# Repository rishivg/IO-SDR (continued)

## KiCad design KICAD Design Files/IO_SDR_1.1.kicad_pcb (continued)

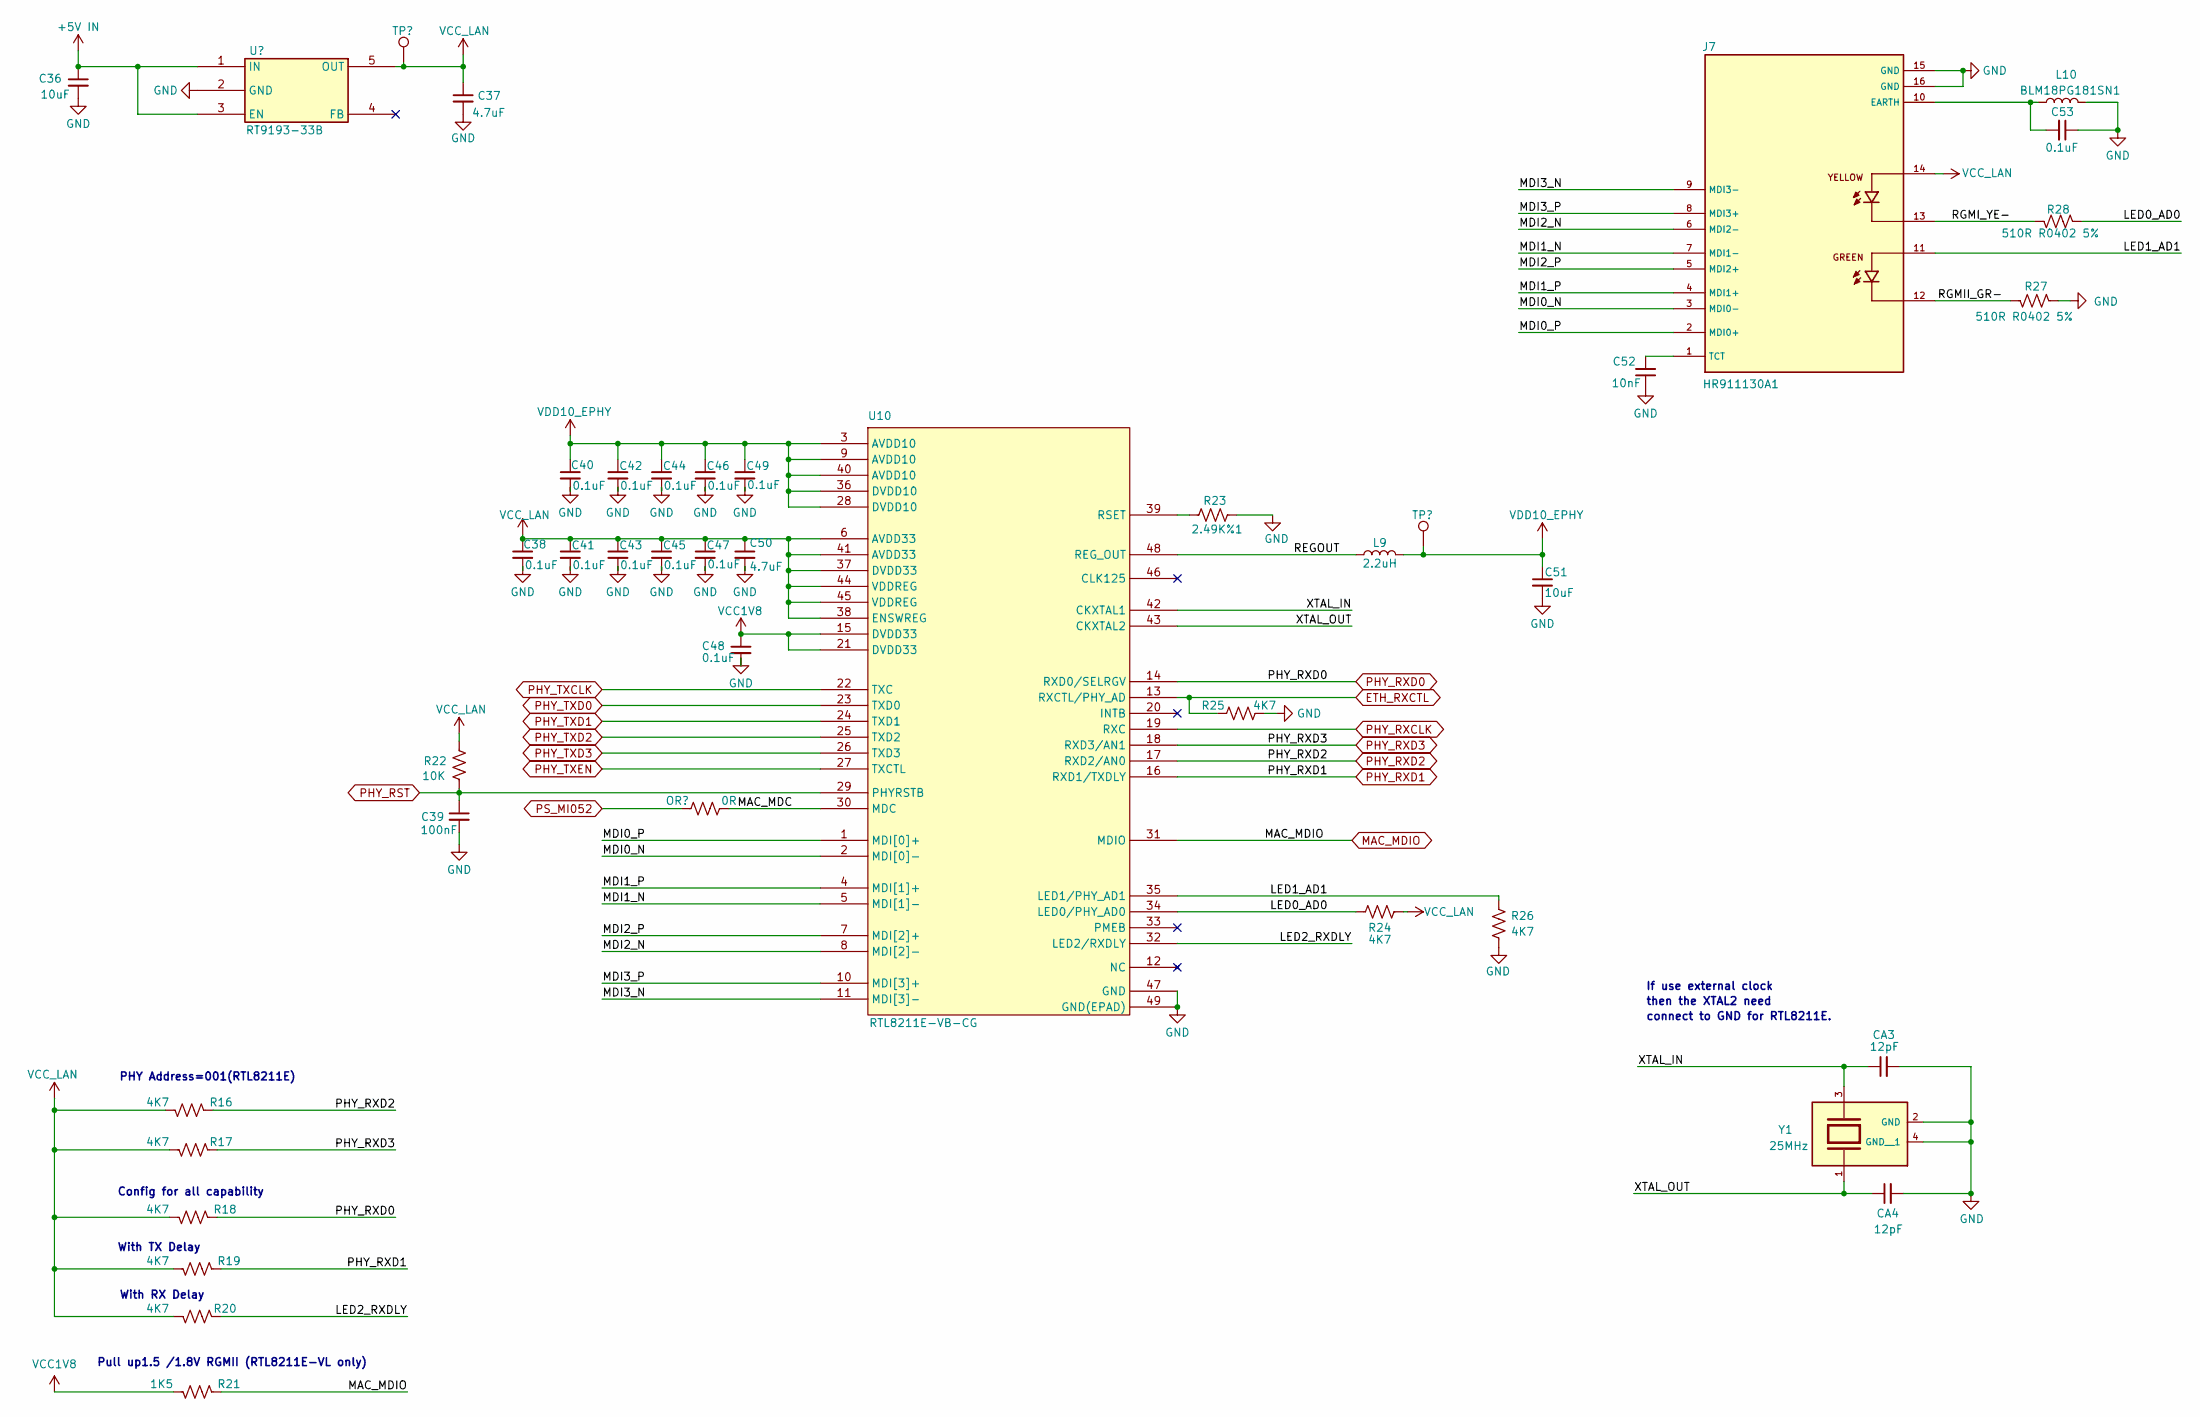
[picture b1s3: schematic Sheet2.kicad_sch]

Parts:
C36: 10uF; C_0603_1608Metric
C37, C50: 4.7uF; C_0603_1608Metric_Pad1.08x0.95mm_HandSolder
C38, C40, C41, C42, C43, C44, C45, C46, C47, C48, C49: 0.1uF; C_0402_1005Metric_Pad0.74x0.62mm_HandSolder
C39: 100nF; C_0402_1005Metric_Pad0.74x0.62mm_HandSolder
C51: 10uF; C_0805_2012Metric_Pad1.18x1.45mm_HandSolder
C52: 10nF; C_0402_1005Metric_Pad0.74x0.62mm_HandSolder
C53: 0.1uF; C_0805_2012Metric_Pad1.18x1.45mm_HandSolder
CA3, CA4: 12pF; C_0402_1005Metric_Pad0.74x0.62mm_HandSolder
J7: HR911130A1; HR911130A_HAN
L9: 2.2uH; L_0603_1608Metric_Pad1.05x0.95mm_HandSolder
L10: BLM18PG181SN1; L_0603_1608Metric_Pad1.05x0.95mm_HandSolder
R16, R17, R18, R19, R20, R24, R25, R26: 4K7; R_0402_1005Metric_Pad0.72x0.64mm_HandSolder
R21: 1K5; R_0402_1005Metric_Pad0.72x0.64mm_HandSolder
R22: 10K; R_0402_1005Metric_Pad0.72x0.64mm_HandSolder
R23: 2.49K%1; R_0402_1005Metric_Pad0.72x0.64mm_HandSolder
R27, R28: 510R R0402 5%; R_0402_1005Metric_Pad0.72x0.64mm_HandSolder
RA5: 0R; R_0603_1608Metric_Pad0.98x0.95mm_HandSolder
TP13, TP14: TestPoint; TestPoint_Pad_D1.0mm
U9: RT9193-33B
U10: RTL8211E-VB-CG
Y1: 25MHz; XTAL_TSX-3225_25.0000MF10P-C0; PARTREV N/A

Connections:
+1V8: C48.1, R21.1, U10.15 (DVDD33), U10.21 (DVDD33); also elsewhere on the board
+36V: C40.1, C42.1, C44.1, C46.1, C49.1, C51.1, L9.2, TP14.1, U10.3 (AVDD10), U10.9 (AVDD10), U10.28 (DVDD10), U10.36 (DVDD10), U10.40 (AVDD10)
/Sheet2/LED0_AD0: R24.2, R28.2, U10.34 (LED0/PHY_AD0)
/Sheet2/LED1_AD1: J7.11, R26.2, U10.35 (LED1/PHY_AD1)
/Sheet2/LED2_RXDLY: R20.2, U10.32 (LED2/RXDLY)
/Sheet2/MAC_MDC: RA5.1, U10.30 (MDC)
/Sheet2/MDI0_N: J7.3 (MDI0-), U10.2 (MDI[0]-)
/Sheet2/MDI0_P: J7.2 (MDI0+), U10.1 (MDI[0]+)
/Sheet2/MDI1_N: J7.7 (MDI1-), U10.5 (MDI[1]-)
/Sheet2/MDI1_P: J7.4 (MDI1+), U10.4 (MDI[1]+)
/Sheet2/MDI2_N: J7.6 (MDI2-), U10.8 (MDI[2]-)
/Sheet2/MDI2_P: J7.5 (MDI2+), U10.7 (MDI[2]+)
/Sheet2/MDI3_N: J7.9 (MDI3-), U10.11 (MDI[3]-)
/Sheet2/MDI3_P: J7.8 (MDI3+), U10.10 (MDI[3]+)
/Sheet2/REGOUT: L9.1, U10.48 (REG_OUT)
/Sheet2/RGMII_GR-: J7.12, R27.1
/Sheet2/RGMI_YE-: J7.13, R28.1
/Sheet2/XTAL_IN: CA3.1, U10.42 (CKXTAL1), Y1.3
/Sheet2/XTAL_OUT: CA4.1, U10.43 (CKXTAL2), Y1.1
ETH_RXCTL: R25.2, U10.13 (RXCTL/PHY_AD); also elsewhere on the board
GND: C36.2, C37.2, C38.2, C39.2, C40.2, C41.2, C42.2, C43.2, C44.2, C45.2, C46.2, C47.2, C48.2, C49.2, C50.2, C51.2, C52.1, C53.1, CA3.2, CA4.2, J7.15 (GND), J7.16 (GND), L10.1, R23.1, R25.1, R26.1, R27.2, U9.2 (GND), U10.47 (GND), U10.49 (GND(EPAD)), Y1.2 (GND), Y1.4 (GND__1); also elsewhere on the board
MAC_MDIO: R21.2, U10.31 (MDIO); also elsewhere on the board
unnamed: C53.2, J7.10 (EARTH), L10.2
unnamed: C52.2, J7.1 (TCT)
unnamed: R23.2, U10.39 (RSET)
PHY_RST: C39.1, R22.1, U10.29 (PHYRSTB)
PHY_RXCLK: U10.19 (RXC); also elsewhere on the board
PHY_RXD0: R18.2, U10.14 (RXD0/SELRGV); also elsewhere on the board
PHY_RXD1: R19.2, U10.16 (RXD1/TXDLY); also elsewhere on the board
PHY_RXD2: R16.2, U10.17 (RXD2/AN0); also elsewhere on the board
PHY_RXD3: R17.2, U10.18 (RXD3/AN1); also elsewhere on the board
PHY_TXCLK: U10.22 (TXC); also elsewhere on the board
PHY_TXD0: U10.23 (TXD0); also elsewhere on the board
PHY_TXD1: U10.24 (TXD1); also elsewhere on the board
PHY_TXD2: U10.25 (TXD2); also elsewhere on the board
PHY_TXD3: U10.26 (TXD3); also elsewhere on the board
PHY_TXEN: U10.27 (TXCTL); also elsewhere on the board
PS_MI052: RA5.2; also elsewhere on the board
VCC: C37.1, C38.1, C41.1, C43.1, C45.1, C47.1, C50.1, J7.14, R16.1, R17.1, R18.1, R19.1, R20.1, R22.2, R24.1, TP13.1, U9.5 (OUT), U10.6 (AVDD33), U10.37 (DVDD33), U10.38 (ENSWREG), U10.41 (AVDD33), U10.44 (VDDREG), U10.45 (VDDREG)

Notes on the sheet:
then the XTAL2 need
PHY Address=001(RTL8211E)
With RX Delay
Pull up1.5 /1.8V RGMII (RTL8211E-VL only)
connect to GND for RTL8211E.
If use external clock
Config for all capability
With TX Delay

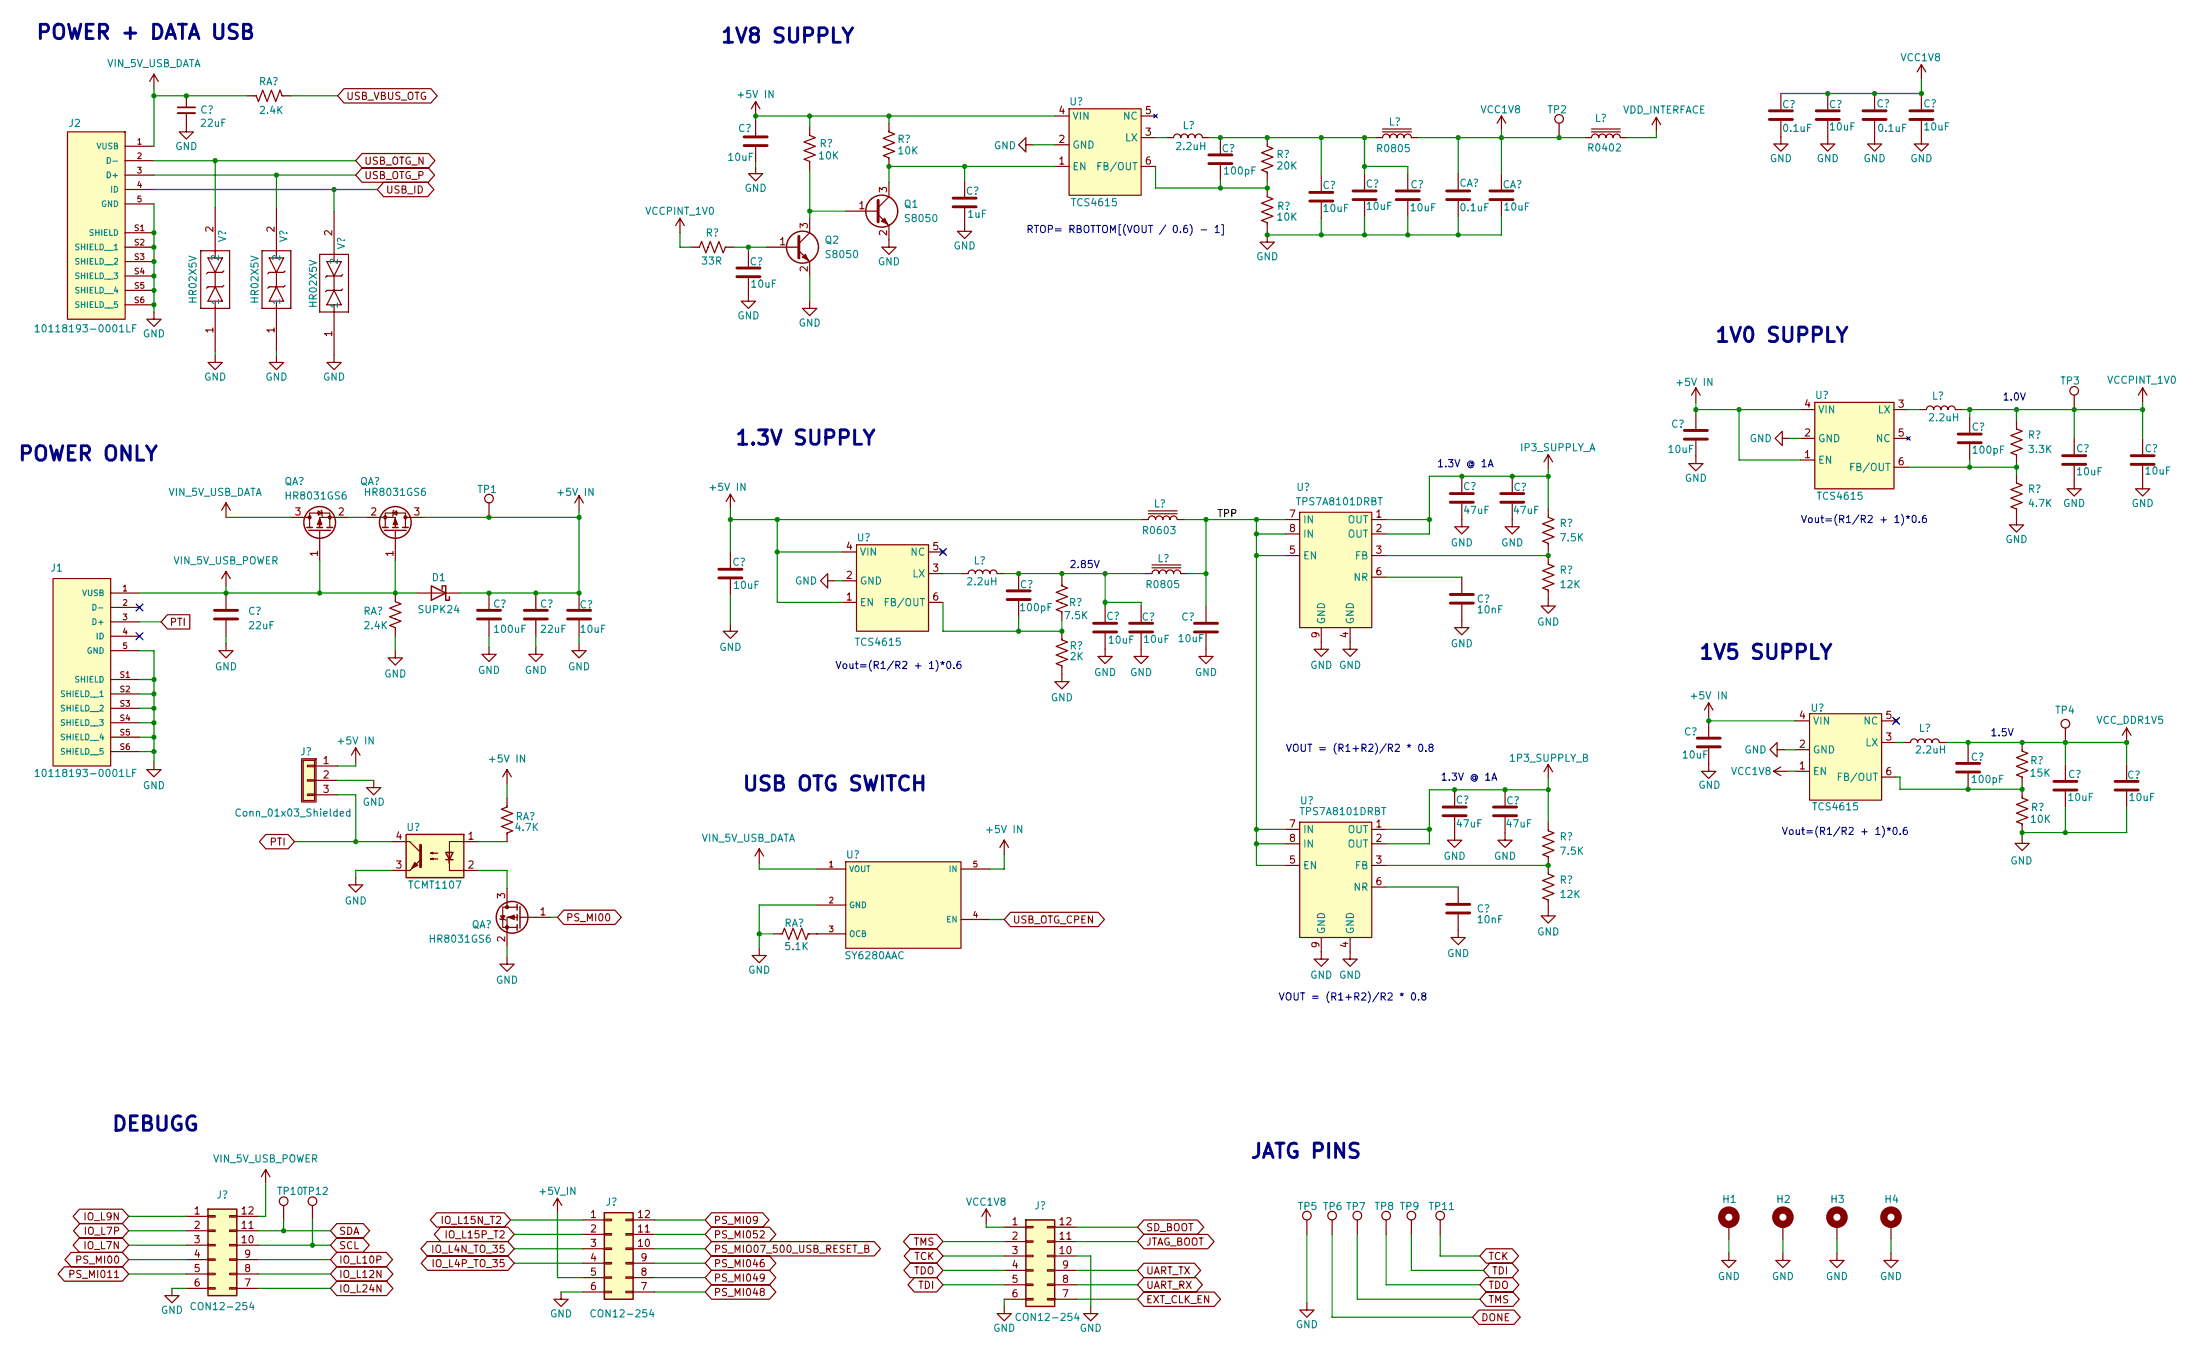
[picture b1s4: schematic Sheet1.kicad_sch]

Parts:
C1, C2: 22uF; C_1206_3216Metric_Pad1.33x1.80mm_HandSolder
C3: 100uF; C_0805_2012Metric_Pad1.18x1.45mm_HandSolder
C4: 22uF; C_0805_2012Metric_Pad1.18x1.45mm_HandSolder
C5: 10uF; C_0805_2012Metric_Pad1.18x1.45mm_HandSolder
C6, C11, C12, C13, C15, C16, C18, C19, C25, C28, C29, C32, C33, C34, C35: 10uF; C_0603_1608Metric_Pad1.08x0.95mm_HandSolder
C7, C8: 10uF; C_1206_3216Metric_Pad1.33x1.80mm_HandSolder
C9: 1uF; C_0805_2012Metric_Pad1.18x1.45mm_HandSolder
C10, C14, C30, C31: 100pF; C_0402_1005Metric_Pad0.74x0.62mm_HandSolder
C17, C20: 0.1uF; C_0402_1005Metric_Pad0.74x0.62mm_HandSolder
C21, C23, C26, C27: 47uF; C_1206_3216Metric_Pad1.33x1.80mm_HandSolder
C22, C24: 10nF; C_0402_1005Metric_Pad0.74x0.62mm_HandSolder
CA1: 0.1uF; C_0402_1005Metric_Pad0.74x0.62mm_HandSolder
CA2: 10uF; C_0603_1608Metric_Pad1.08x0.95mm_HandSolder
D1: SUPK24; D_SOD-123
H1, H2, H3, H4: MountingHole_Pad; MountingHole_2.5mm_Pad
J1, J2: 10118193-0001LF; AMPHENOL_10118193-0001LF; PARTREV E
J3: Conn_01x03_Shielded; PinHeader_1x03_P2.54mm_Vertical
J4, J5, J6: CON12-254; PinHeader_2x06_P2.54mm_Vertical
L1, L4, L7, L8: 2.2uH; L_0603_1608Metric_Pad1.05x0.95mm_HandSolder
L2: R0603; L_0603_1608Metric_Pad1.05x0.95mm_HandSolder
L3, L5: R0805; L_0805_2012Metric_Pad1.05x1.20mm_HandSolder
L6: R0402; L_0402_1005Metric_Pad0.77x0.64mm_HandSolder
Q1, Q2: S8050; SOT-23
QA1, QA2, QA3: HR8031GS6
R1: 33R; R_0402_1005Metric_Pad0.72x0.64mm_HandSolder
R2, R3, R7, R15: 10K; R_0402_1005Metric_Pad0.72x0.64mm_HandSolder
R4, R8, R10: 7.5K; R_0402_1005Metric_Pad0.72x0.64mm_HandSolder
R5: 2K; R_0402_1005Metric_Pad0.72x0.64mm_HandSolder
R6: 20K; R_0402_1005Metric_Pad0.72x0.64mm_HandSolder
R9, R11: 12K; R_0402_1005Metric_Pad0.72x0.64mm_HandSolder
R12: 3.3K; R_0402_1005Metric_Pad0.72x0.64mm_HandSolder
R13: 4.7K; R_0402_1005Metric_Pad0.72x0.64mm_HandSolder
R14: 15K; R_0402_1005Metric_Pad0.72x0.64mm_HandSolder
RA1, RA2: 2.4K; R_0402_1005Metric_Pad0.72x0.64mm_HandSolder
RA3: 4.7K; R_0603_1608Metric_Pad0.98x0.95mm_HandSolder
RA4: 5.1K; R_0603_1608Metric_Pad0.98x0.95mm_HandSolder
TP1, TP2, TP3, TP4, TP5, TP6, TP7, TP8, TP9, TP10, TP11, TP12: TestPoint; TestPoint_Pad_D1.0mm
U1: TCMT1107; SOP-4_4.4x2.6mm_P1.27mm
U2: SY6280AAC
U3, U4, U7, U8: TCS4615
U5, U6: TPS7A8101DRBT
V1, V2, V3: HR02X5V

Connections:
+1V0: C30.1, C32.1, C35.1, L8.2, R1.1, R12.1, TP3.1; also elsewhere on the board
+1V2: C21.1, C26.1, R10.1, U6.1 (OUT), U6.2 (OUT); also elsewhere on the board
+1V5: C31.1, C33.1, C34.1, L7.2, R14.1, TP4.1; also elsewhere on the board
+1V8: C17.1, C19.1, C20.1, C25.1, CA1.1, CA2.1, J5.1, L5.2, L6.1, TP2.1, U7.1 (EN); also elsewhere on the board
+5VD: C2.1, D1.2 (A), J1.1 (VUSB), J4.12, QA1.1 (G), QA2.1 (G), RA2.1
+5VP: C1.1, J2.1 (VUSB), QA1.3 (D), RA1.2, U2.1 (VOUT)
+12L: C23.1, C27.1, R8.1, U5.1 (OUT), U5.2 (OUT); also elsewhere on the board
+VSW: L6.2; also elsewhere on the board
/Sheet1/TPP: C13.1, L2.2, L3.2, U5.5 (EN), U5.7 (IN), U5.8 (IN), U6.5 (EN), U6.7 (IN), U6.8 (IN)
DONE: TP6.1; also elsewhere on the board
EXT_CLK_EN: J5.7; also elsewhere on the board
GND: C1.2, C2.2, C3.2, C4.2, C5.2, C6.2, C7.2, C8.2, C9.2, C11.2, C12.2, C13.2, C15.2, C16.2, C17.2, C18.2, C19.2, C20.2, C21.2, C22.2, C23.2, C24.2, C25.2, C26.2, C27.2, C28.2, C29.2, C32.2, C33.2, C34.2, C35.2, CA1.2, CA2.2, H1.1, H2.1, H3.1, H4.1, J1.5 (GND), J1.S1 (SHIELD), J1.S2 (SHIELD__1), J1.S3 (SHIELD__2), J1.S4 (SHIELD__3), J1.S5 (SHIELD__4), J1.S6 (SHIELD__5), J2.5 (GND), J2.S1 (SHIELD), J2.S2 (SHIELD__1), J2.S3 (SHIELD__2), J2.S4 (SHIELD__3), J2.S5 (SHIELD__4), J2.S6 (SHIELD__5), J3.2, J4.6, J5.6, J5.10, J6.6, Q1.2 (E), Q2.2 (E), QA3.2 (S), R5.2, R7.2, R9.2, R11.2, R13.2, R15.2, RA2.2, RA4.2, TP5.1, U1.3, U2.2 (GND), U3.2 (GND), U4.2 (GND), U5.4 (GND), U5.9 (GND), U6.4 (GND), U6.9 (GND), U7.2 (GND), U8.2 (GND), V1.1, V2.1, V3.1; also elsewhere on the board
IO_L4N_TO_35: J6.3; also elsewhere on the board
IO_L4P_TO_35: J6.4; also elsewhere on the board
IO_L7N: J4.3; also elsewhere on the board
IO_L7P: J4.2; also elsewhere on the board
IO_L9N: J4.1; also elsewhere on the board
IO_L10P: J4.9; also elsewhere on the board
IO_L12N: J4.8; also elsewhere on the board
IO_L15N_T2: J6.1
IO_L15P_T2: J6.2; also elsewhere on the board
IO_L24N: J4.7; also elsewhere on the board
JTAG_BOOT: J5.11; also elsewhere on the board
unnamed: C10.1, C11.1, C12.1, L1.2, L3.1, R4.1
unnamed: C14.1, C15.1, C16.1, C18.1, L4.2, L5.1, R6.1
unnamed: Q1.1 (B), Q2.3 (C), R2.2
unnamed: C9.1, Q1.3 (C), R3.2, U4.1 (EN)
unnamed: C7.1, Q2.1 (B), R1.2
unnamed: QA1.2 (S), QA2.2 (S)
unnamed: QA3.3 (D), U1.2
unnamed: RA3.2, U1.1
unnamed: RA4.1, U2.3 (OCB)
unnamed: C10.2, R4.2, R5.1, U3.6 (FB/OUT)
unnamed: L1.1, U3.3 (LX)
unnamed: C14.2, R6.2, R7.1, U4.6 (FB/OUT)
unnamed: L4.1, U4.3 (LX)
unnamed: R8.2, R9.1, U5.3 (FB)
unnamed: C24.1, U5.6 (NR)
unnamed: R10.2, R11.1, U6.3 (FB)
unnamed: C22.1, U6.6 (NR)
unnamed: C31.2, R14.2, R15.1, U7.6 (FB/OUT)
unnamed: L7.1, U7.3 (LX)
unnamed: C30.2, R12.2, R13.1, U8.6 (FB/OUT)
unnamed: L8.1, U8.3 (LX)
PS_MI00: J4.4, QA3.1 (G); also elsewhere on the board
PS_MI09: J6.12; also elsewhere on the board
PS_MI011: J4.5; also elsewhere on the board
PS_MI046: J6.9; also elsewhere on the board
PS_MI048: J6.7; also elsewhere on the board
PS_MI049: J6.8; also elsewhere on the board
PS_MI052: J6.11; also elsewhere on the board
PS_MIO07_500_USB_RESET_B: J6.10; also elsewhere on the board
PTI: J1.3 (D+), J3.3, U1.4
SCL: J4.10, TP12.1; also elsewhere on the board
SDA: J4.11, TP10.1; also elsewhere on the board
SD_BOOT: J5.12; also elsewhere on the board
TCK: J5.3, TP11.1; also elsewhere on the board
TDI: J5.5, TP9.1; also elsewhere on the board
TDO: J5.4, TP8.1; also elsewhere on the board
TMS: J5.2, TP7.1; also elsewhere on the board
UART_RX: J5.8; also elsewhere on the board
UART_TX: J5.9; also elsewhere on the board
USB_ID: J2.4 (ID), V3.2; also elsewhere on the board
USB_OTG_CPEN: U2.4 (EN); also elsewhere on the board
USB_OTG_N: J2.2 (D-), V1.2; also elsewhere on the board
USB_OTG_P: J2.3 (D+), V2.2; also elsewhere on the board
USB_VBUS_OTG: RA1.1; also elsewhere on the board

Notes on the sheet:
1.3V @ 1A
POWER + DATA USB
RTOP= RBOTTOM[(VOUT / 0.6) - 1]
POWER ONLY
1V0 SUPPLY
DEBUGG
1.0V
JATG PINS
Vout=(R1/R2 + 1)*0.6
2.85V
1V8 SUPPLY
1.3V SUPPLY
VOUT = (R1+R2)/R2 * 0.8
USB OTG SWITCH
1V5 SUPPLY
1.5V

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
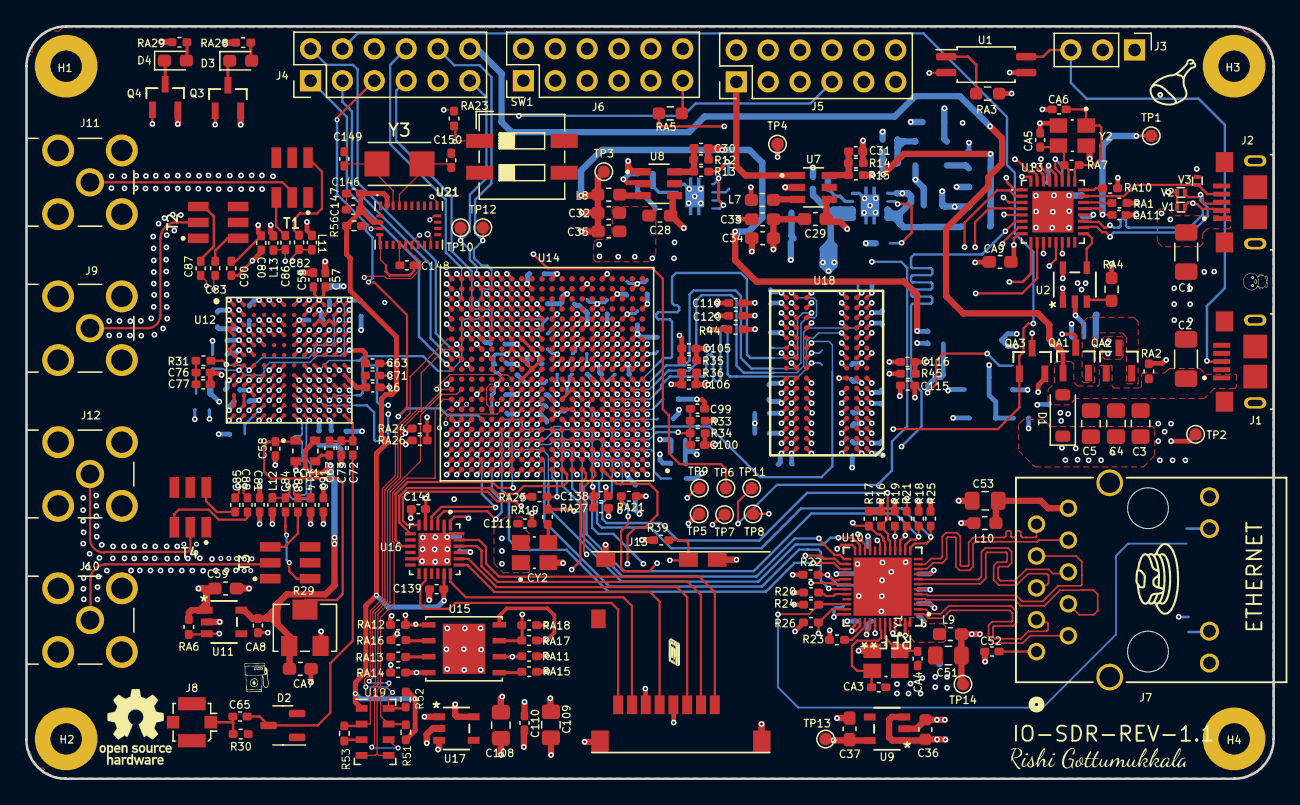
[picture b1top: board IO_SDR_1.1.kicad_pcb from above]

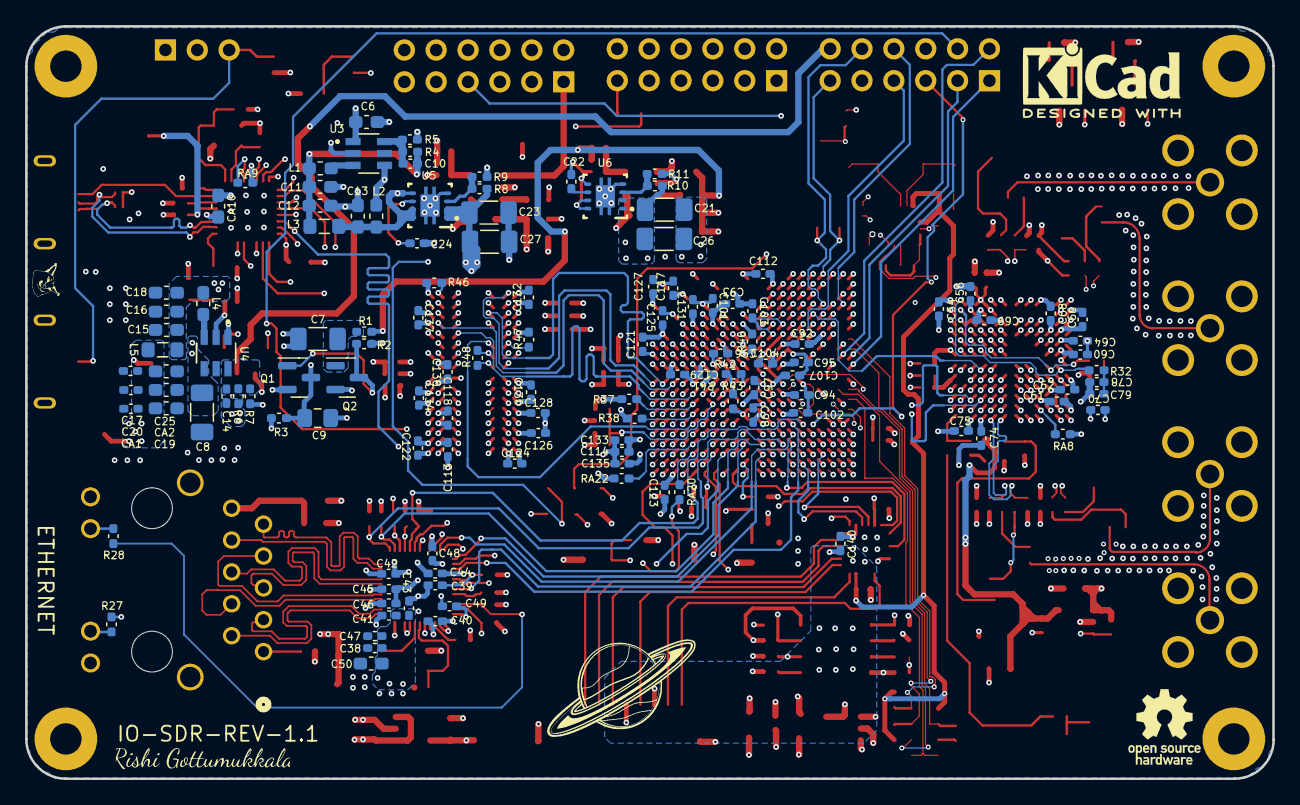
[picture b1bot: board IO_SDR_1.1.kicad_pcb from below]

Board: 8 copper layers, 99.4 x 60.0 mm, 327 parts (125 on the bottom side), 299 nets.

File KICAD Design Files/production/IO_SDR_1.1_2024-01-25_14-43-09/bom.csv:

Designator,Footprint,Quantity,Value,LCSC Part #
"C1, C2",1206,2,22uF,
"C10, C119, C120, C14, C30, C31",0402,6,100pF,
"C100, C105, C106, C110, C115, C116, C139, C140, C141, C146, C147, C39, C80, C81, C90, C91, C99",0402,17,100nF,
"C101, C102, C103, C104, C107, C138, C17, C20, C38, C40, C41, C42, C43, C44, C45, C46, C47, C48, C49, C92, C93, C97, C98, CA1, CA11, CA8",0402,26,0.1uF,
"C108, C109, C5, C51",0805,4,10uF,
"C11, C12, C13, C15, C16, C18, C19, C25, C28, C29, C32, C33, C34, C35, C36, C59, C6, CA2, CA7, CA9",0603,20,10uF,
"C111, C112, C114, C118, C148, C56, C57, C58, C62, C63, C68, C70",0402,12,1uF,
"C113, C135, C94, C95, C96",0402,5,10uF,
"C117, C121, C122, C123, C124, C125, C126, C127, C128, C129, C130, C131, C132, C133, C134, C136, C137, C22, C24, C52, C54, C55, C60, C61, C64, C66, C69, C71, C74, C75",0402,30,10nF,
"C149, C150",0402,2,22pf,
"C21, C23, C26, C27",1206,4,47uF,
C3,0805,1,100uF,
"C37, C50, CA10",0603,3,4.7uF,
C4,0805,1,22uF,
C53,0805,1,0.1uF,
"C65, C67, C72, C73, C82, C83, C84, C85, C86, C87, C88, C89, CA5, CA6",0402,14,18pF,
"C7, C8",1206,2,10uF,
"C76, C77, C78, C79",0402,4,1nF,
C9,0805,1,1uF,
"CA3, CA4",0402,2,12pF,
CY1,XTAL_ASDMB-33.333MHZ-LC-T,1,ASDMB-33.333MHZ-LC-T,
CY2,XTAL_ABM8AIG-25.000MHZ-12-2Z-T3,1,33.333MHz,
D1,D_SOD-123,1,SUPK24,
D2,SOT-23-3,1,SUP5522F,
"D3, D4",0603,2,LED6,
"H1, H2, H3, H4",MountingHole_2.5mm_Pad,4,MountingHole_Pad,
"J1, J2",AMPHENOL_10118193-0001LF,2,10118193-0001LF,
"J10, J11, J12, J9",ADAMTECH_RF2-49B-T-00-50-G-HDW,4,RF2-49B-T-00-50-G-HDW,
J13,MOLEX_502570-0893,1,502570-0893,
J3,PinHeader_1x03_P2.54mm_Vertical,1,Conn_01x03_Shielded,
"J4, J5, J6",PinHeader_2x06_P2.54mm_Vertical,3,CON12-254,
J7,HR911130A_HAN,1,HR911130A1,
J8,U.FL_Molex_MCRF_73412-0110_Vertical,1,73412-0110,
"L1, L4, L7, L8, L9",0603,5,2.2uH,
L10,0603,1,BLM18PG181SN1,
"L11, L13",0402,2,330nH,
"L12, L14",0402,2,330nF,
L2,0603,1,R0603,
"L3, L5",0805,2,R0805,
L6,0402,1,R0402,
"Q1, Q2",SOT-23,2,S8050,
"Q3, Q4",SOT23 MOSFET FOOT PRINT,2,~,
"QA1, QA2, QA3",HR8031GS6,3,HR8031GS6,
"R1, RA19, RA20",0402,3,33R,
"R10, R4, R8",0402,3,7.5K,
"R11, R9",0402,2,12K,
R12,0402,1,3.3K,
"R13, R39, R40, R41, R42, R43, R46, R51, R52, R53, RA28, RA29",0402,12,4.7K,
R14,0402,1,15K,
"R15, R2, R22, R3, R56, R7, RA6",0402,7,10K,
"R16, R17, R18, R19, R20, R24, R25, R26",0402,8,4K7,
R21,0402,1,1K5,
R23,0402,1,2.49K%1,
"R27, R28",0402,2,510R R0402 5%,
R29,Potentiometer_Bourns_3214W_Vertical,1,50K,
R30,0402,1,ESD,
"R31, R32",0402,2,1R,
"R33, R34, R35, R36, R44, R45, RA1, RA2",0402,8,2.4K,
"R37, R38, R48",0402,3,80.5R,
R47,0402,1,240R,
R5,0402,1,2K,
"R6, RA11, RA13, RA15, RA16, RA17, RA21, RA22, RA23, RA25, RA27, RA9",0402,12,20K,
RA10,0402,1,8.06K,
"RA12, RA14, RA18",0402,3,1K,
"RA24, RA26",0402,2,100K,
RA3,0603,1,4.7K,
RA4,0603,1,5.1K,
RA5,0603,1,0R,
RA7,0402,1,1M,
RA8,0402,1,14.3K,
SW1,SW_DIP_SPSTx02_Slide_6.7x6.64mm_W6.73mm_P2.54mm_LowProfile_JPin,1,SW_DIP_x02,
"T1, T2, T3, T4",XFMR_TCM1-63AX_,4,TCM1-63AX_,
"TP1, TP10, TP11, TP12, TP13, TP14, TP2, TP3, TP4, TP5, TP6, TP7, TP8, TP9",TestPoint_Pad_D1.0mm,14,TestPoint,
U1,SOP-4_4.4x2.6mm_P1.27mm,1,TCMT1107,
U10,RTL8211E-VB-CG,1,RTL8211E-VB-CG,
"U11, U17, U9",RT9193-33B,3,RT9193-33B,
U12,AD9361BBCZ,1,AD9361BBCZ,
U13,USB3320C-EZK-TR,1,USB3320C-EZK-TR,
U14,XC7Z010-1CLG400I,1,XC7Z010-1CLG400I,
U15,MX25U1635EZNI-10G,1,MX25U1635EZNI-10G,
U16,TXS02612RTWR,1,TXS02612RTWR,
U18,H5TQ4G63AFR,1,H5TQ4G63AFR,
U19,LGA-8_3x5mm_P1.25mm,1,MS5611-01BA,
U2,SY6280AAC,1,SY6280AAC,
U21,IC_BNO080,1,BNO085,
"U3, U7, U8",TCS4615,3,TCS4615,
U4,TCS4615,1,TCS4615 ,
"U5, U6",TPS7A8101DRBT,2,TPS7A8101DRBT,
"V1, V2, V3",HR02X5V,3,HR02X5V,
Y1,XTAL_TSX-3225_25.0000MF10P-C0,1,25MHz,TSX-3225_25.0000MF10P-C0
Y2,XTAL_TSX-3225_25.0000MF10P-C0,1,25MHz ,
Y3,Crystal_SMD_Qantek_QC5CB-2Pin_5x3.2mm,1,32.768kHz,

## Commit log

2023-12-16 Progress and Commit
    Progress and Commit
2023-12-17 Added
    Added
2023-12-18 Big Cleanup
    Big Cleanup
2023-12-18 Added labels, need to do power last
    Added labels, need to do power last
2024-01-25 1.1 revision
    1.1 revision
2024-01-25 Added Balun 3D models + fixes
    Added Balun 3D models + fixes
2024-02-07 Fixing prod files
    Fixing prod files
2024-02-08 Added ferrite bead cores
    Added ferrite bead cores
2024-08-26 Added Renders
    Added Renders
